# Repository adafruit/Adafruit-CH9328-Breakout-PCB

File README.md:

## Adafruit CH9328 UART to HID Keyboard Breakout PCB

<a href="http://www.adafruit.com/products/5973"><br/>
Click here to purchase one from the Adafruit shop</a>

PCB files for the Adafruit CH9328 UART to HID Keyboard Breakout. 

Format is EagleCAD schematic and board layout
* https://www.adafruit.com/product/5973

### Description

We love using chips with 'native USB' peripherals - that's the magic silicon that lets a microcontroller act like an HID keyboard or mouse or disk drive or MIDI synth. It's a standard addition on SAMD21, RP2040, and even the latest ESP32-S2 and ESP32-S3 boards. But what about when you have a classic ATmega328 Uno? or an original ESP32 or ESP8266? Maybe even a single-board computer like a Raspberry Pi? We would say "sorry...that's not possible"  UNTIL NOW!

The CH9328 is a funky chip that is basically a programmed microcontroller that enumerates as an every-day HID keyboard and can convert ASCII or 8-byte raw reports, read over a standard serial port UART, into keypresses. So, you can emulate a keyboard even if your chip doesn't have native USB! You do need a hardware or software serial port: some way to generate 9600 baud 3V-logic signal that the CH9328 can read.

We added all the support circuitry to make this chip easy to use, you may not even need to do any soldering. The CH9328 is connected to a USB Type C port so it's easy to plug into any computer, laptop or even phone/tablet. Then, you can get 5V power from the 5V and Ground pads. There's a UART RX receive input plus a reset line if you want to perform a hard reset. If you want 'solderless' functionality, grab one of our JST SH cables: the red line will provide 5V, black is Ground, and the white wire is data in. 

You can configure the 'Mode' using the 4 on-board switches, do that before powering it up:

* Switch #1 is used to configure the "Upload speed" - for most cases it doesn't matter which way its set
* If Switch #2, #3 and #4 are all 'ON' the chip is in Mode 0:
Visible ASCII characters are sent as-is: if you send ASCII "A", an "A" is typed. If 0x1B is received, it is converted to the Enter key
* If Switch #2 and #4 are 'ON' and Switch #3 is 'OFF' the chip is in Mode 1:
Visible ASCII characters are sent as-is: if you send ASCII "A", an "A" is typed
* If Switch #2 and #3 are 'ON' and Switch #4 is 'OFF' the chip is in Mode 2:
Visible ASCII characters are sent as-is: if you send ASCII "A", an "A" is typed. If 0x28 is received, it is converted to the Enter key
* If Switch #3 and #4 are 'ON' and Switch #2 is 'OFF' the chip is in Mode 3:
This is the mode for sending raw 8-byte HID reports. This is also good if you want more control over the keypresses, or keyholds, or to mimic a non-US keyboard because you can control exactly what control codes are sent and when.

We recommend using mode 3 if possible, but you'll want to use our CH9328 library to do so.

This is a nice and easy way to emulate a keyboard without having to worry about native USB support, gadget mode, or maybe you just want to emulate more than one kind of device. You can also do 'funky' things like have one desktop or single-board computer 'type' into a device such as a computer or mobile device by running our Python code and having it send UART data via a USB-to-UART converter. Either way, the CH9328 will make it easy to keeb away.

### License

Adafruit invests time and resources providing this open source design, please support Adafruit and open-source hardware by purchasing products from [Adafruit](https://www.adafruit.com)!

Designed by Limor Fried/Ladyada for Adafruit Industries.

Creative Commons Attribution/Share-Alike, all text above must be included in any redistribution. 
See license.txt for additional details.

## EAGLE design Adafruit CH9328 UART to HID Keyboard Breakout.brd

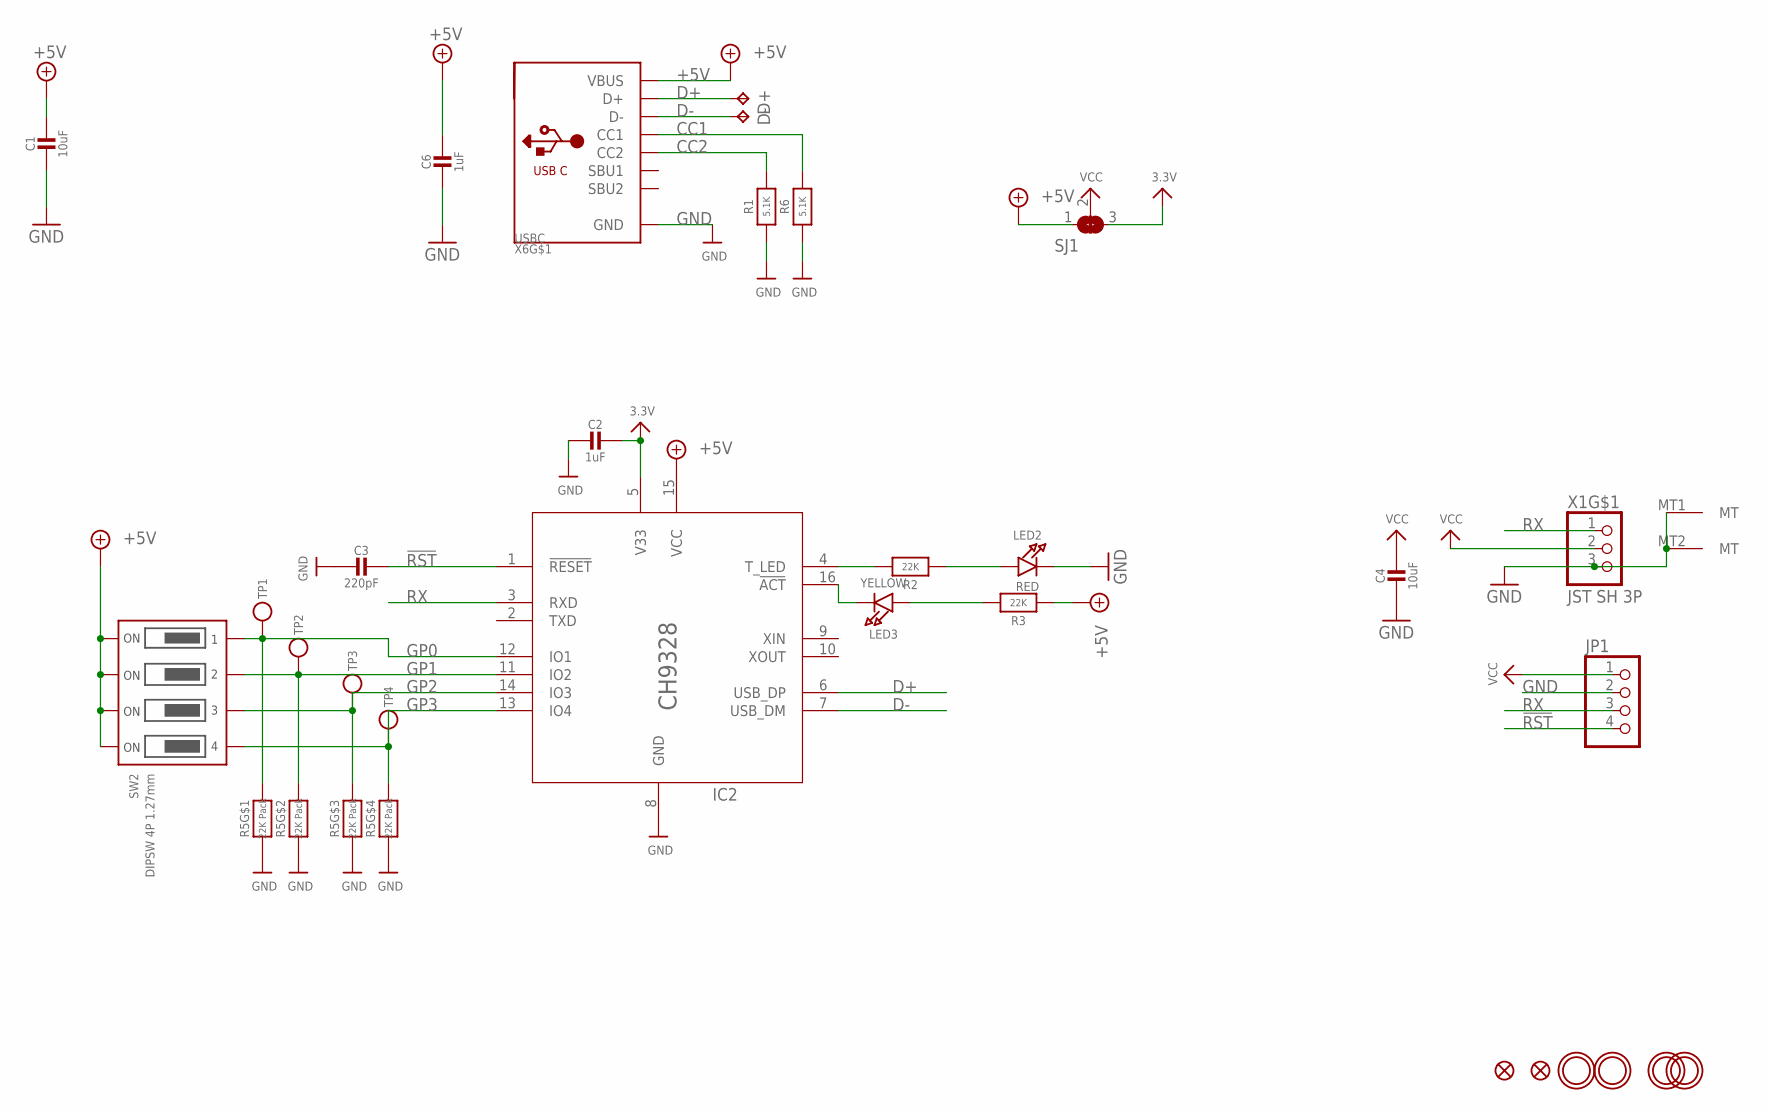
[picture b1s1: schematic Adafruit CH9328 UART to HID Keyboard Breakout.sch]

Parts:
C1, C4: 10uF; 0805-NO
C2, C6: 1uF; 0603-NO
C3: 220pF; 0603-NO
D+: TPTP17R; TP17R
D-: TPTP17R; TP17R
FID1, FID2: FIDUCIAL_0.5MM
IC2: CH9328_SKINNY; SO16_SKINNY
JP1: HEADER-1X4ROUND; 1X04_ROUND
LED2: RED; CHIPLED_0603_NOOUTLINE
LED3: YELLOW; CHIPLED_0603_NOOUTLINE
R1, R6: 5.1K; 0603-NO
R2, R3: 22K; 0603-NO
R5: 22K Pack; RESPACK_4X0603
SJ1: SOLDERJUMPER_2WAY; SOLDERJUMPER_2WAY_OPEN_NOPASTE
SW2: DIPSW 4P 1.27mm; DIPSWITCH_4PIN_1.27
TP1, TP2, TP3, TP4: TESTPOINTROUND1.5MMNO; TESTPOINT_ROUND_1.5MM_NO
U$2, U$3, U$6, U$7: MOUNTINGHOLE2.5; MOUNTINGHOLE_2.5_PLATED
X1: JST SH 3P; JST_SH3
X6: USBC; USB_C_CUSB31-CFM2AX-01-X

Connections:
3.3V: C2.1, IC2.5 (V33), SJ1.3
!RST: C3.1, IC2.1 (!RESET), JP1.4
+5V: C1.1, C6.1, IC2.15 (VCC), R3.1, SJ1.1, SW2.1ON, SW2.2ON, SW2.3ON, SW2.4ON, X6.A4B9 (VBUS), X6.B4A9 (VBUS)
CC1: R6.2, X6.A5 (CC1)
CC2: R1.2, X6.B5 (CC2)
D+: D+.TP, IC2.6 (USB_DP), X6.A6 (D+), X6.B6 (D+)
D-: D-.TP, IC2.7 (USB_DM), X6.A7 (D-), X6.B7 (D-)
GND: C1.2, C2.2, C3.2, C4.2, C6.2, IC2.8 (GND), JP1.2, LED2.C, R1.1, R5.1, R5.2 (1), R5.3 (1), R5.4 (1), R6.1, X1.3, X1.MT1 (MT), X1.MT2 (MT), X6.A1B12 (GND), X6.B1A12 (GND)
GP0: IC2.12 (IO1), R5.8 (2), SW2.1OFF, TP1.P$1
GP1: IC2.11 (IO2), R5.7 (2), SW2.2OFF, TP2.P$1
GP2: IC2.14 (IO3), R5.6 (2), SW2.3OFF, TP3.P$1
GP3: IC2.13 (IO4), R5.5 (2), SW2.4OFF, TP4.P$1
unnamed: IC2.4 (T_LED), R2.2
unnamed: LED2.A, R2.1
unnamed: LED3.A, R3.2
unnamed: IC2.16 (!ACT), LED3.C
RX: IC2.3 (RXD), JP1.3, X1.1
VCC: C4.1, JP1.1, SJ1.2, X1.2

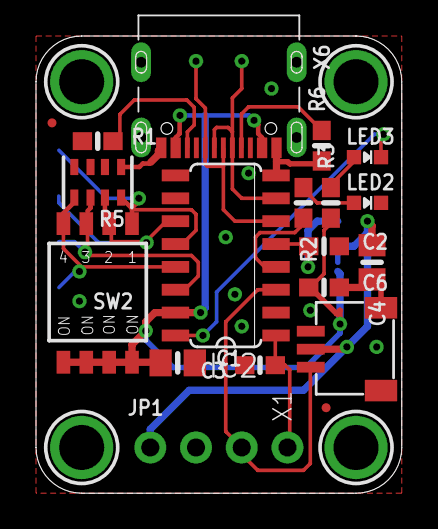
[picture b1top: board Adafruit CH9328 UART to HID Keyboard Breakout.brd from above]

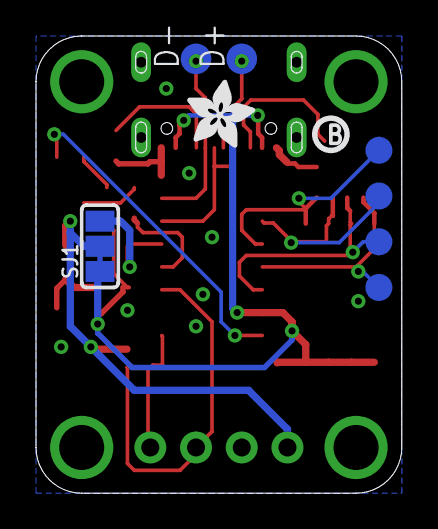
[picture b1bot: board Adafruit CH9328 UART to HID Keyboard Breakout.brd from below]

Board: 2 copper layers, 20.3 x 25.4 mm, 55 parts (20 on the bottom side), 18 nets.

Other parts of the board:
PLABEL0: PLABEL0
PLABEL1: PLABEL1
PLABEL2: PLABEL2
PLABEL3: PLABEL3
PLABEL4: PLABEL4
PLABEL5: PLABEL5
PLABEL6: PLABEL6
PLABEL7: PLABEL7
PLABEL8: PLABEL8
PLABEL9: PLABEL9
PLABEL10: PLABEL10
PLABEL11: PLABEL11
PLABEL12: PLABEL12
PLABEL13: PLABEL13
PLABEL14: PLABEL14
PLABEL15: PLABEL15
PLABEL16: PLABEL16
PLABEL17: PLABEL17
PLABEL18: PLABEL18
PLABEL19: PLABEL19
PLABEL20: PLABEL20
PLABEL21: PLABEL21
PLABEL22: PLABEL22
U$17: ADAFRUIT_3.5MM
U$18: PCBFEAT-REV-040

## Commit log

2024-06-07 cookiecutter

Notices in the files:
parts and their libraries:
microbuilder: This work is placed in the public domain, and may be freely used for commercial and non-commercial work with the following conditions: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
